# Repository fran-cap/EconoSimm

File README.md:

# EconoSimm
## A low cost Rom for SE/30 machines and compatables
Simply put this allows for a custom rom to be installed inside of a se/30 to skip things like the built in RAM check.
You can also use any extra space to fit in a small system file.

I've based this off of the work of [Doug Brown](https://www.downtowndougbrown.com/category/mac-rom-hacking/).
And GGlabs [MACSIMM](https://gglabs.us/node/2019).

You can find information about making a rom [here](http://www.bigmessowires.com/mac-rom-inator-ii/) (shoutouts to BMOW)
And how to make a custom disk image [here](http://www.bigmessowires.com/2016/07/22/rom-disk-creation-with-rom-inator-ii/).

The max size of any rom image will depend on the size of the flash chips you use but the max is 4 4mb chips or 2MB in total.
You can split any rom file you make into 4 pieces using the tool of your choice and burn that to each of the 4 chips.

## Note: The pcb has to be 1.2MM thick (approx) or it will not fit into a rom socket!

### You can program the chips individually with a standard flash programmer and a 32 PLCC -> dip adapter
BMOW's programmer may work but I have not tested it.

#### I'm not liable if this damages your Macintosh

## Replaces this:

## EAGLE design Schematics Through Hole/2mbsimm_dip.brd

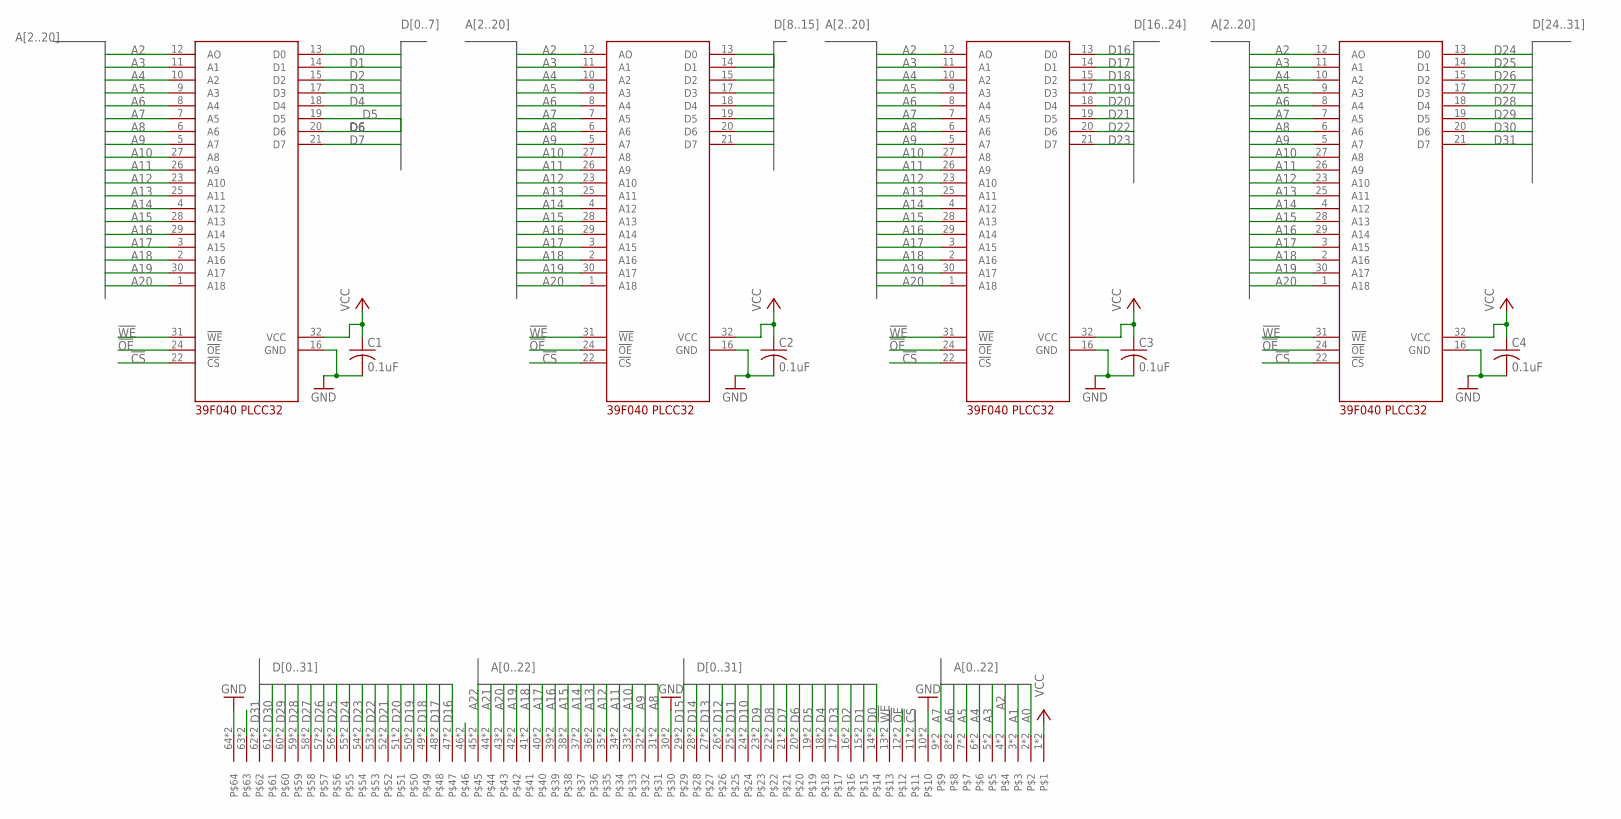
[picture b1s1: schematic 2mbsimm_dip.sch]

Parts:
C1, C2, C3, C4: 0.1uF; C1206
CON1: MYSIMM; SIMM64L
U$1, U$2, U$3, U$4: 39F040-PLCC-SOCKET-DIP; S32

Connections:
!CS: CON1.11, CON1.75, U$1.22 (!CS), U$2.22 (!CS), U$3.22 (!CS), U$4.22 (!CS)
!OE: CON1.12, CON1.76, U$1.24 (!OE), U$2.24 (!OE), U$3.24 (!OE), U$4.24 (!OE)
!WE: CON1.13, CON1.77, U$1.31 (!WE), U$2.31 (!WE), U$3.31 (!WE), U$4.31 (!WE)
A0: CON1.2, CON1.66
A1: CON1.3, CON1.67
A2: CON1.4, CON1.68, U$1.12 (AO), U$2.12 (AO), U$3.12 (AO), U$4.12 (AO)
A3: CON1.5, CON1.69, U$1.11 (A1), U$2.11 (A1), U$3.11 (A1), U$4.11 (A1)
A4: CON1.6, CON1.70, U$1.10 (A2), U$2.10 (A2), U$3.10 (A2), U$4.10 (A2)
A5: CON1.7, CON1.71, U$1.9 (A3), U$2.9 (A3), U$3.9 (A3), U$4.9 (A3)
A6: CON1.8, CON1.72, U$1.8 (A4), U$2.8 (A4), U$3.8 (A4), U$4.8 (A4)
A7: CON1.9, CON1.73, U$1.7 (A5), U$2.7 (A5), U$3.7 (A5), U$4.7 (A5)
A8: CON1.31, CON1.95, U$1.6 (A6), U$2.6 (A6), U$3.6 (A6), U$4.6 (A6)
A9: CON1.32, CON1.96, U$1.5 (A7), U$2.5 (A7), U$3.5 (A7), U$4.5 (A7)
A10: CON1.33, CON1.97, U$1.27 (A8), U$2.27 (A8), U$3.27 (A8), U$4.27 (A8)
A11: CON1.34, CON1.98, U$1.26 (A9), U$2.26 (A9), U$3.26 (A9), U$4.26 (A9)
A12: CON1.35, CON1.99, U$1.23 (A10), U$2.23 (A10), U$3.23 (A10), U$4.23 (A10)
A13: CON1.36, CON1.100, U$1.25 (A11), U$2.25 (A11), U$3.25 (A11), U$4.25 (A11)
A14: CON1.37, CON1.101, U$1.4 (A12), U$2.4 (A12), U$3.4 (A12), U$4.4 (A12)
A15: CON1.38, CON1.102, U$1.28 (A13), U$2.28 (A13), U$3.28 (A13), U$4.28 (A13)
A16: CON1.39, CON1.103, U$1.29 (A14), U$2.29 (A14), U$3.29 (A14), U$4.29 (A14)
A17: CON1.40, CON1.104, U$1.3 (A15), U$2.3 (A15), U$3.3 (A15), U$4.3 (A15)
A18: CON1.41, CON1.105, U$1.2 (A16), U$2.2 (A16), U$3.2 (A16), U$4.2 (A16)
A19: CON1.42, CON1.106, U$1.30 (A17), U$2.30 (A17), U$3.30 (A17), U$4.30 (A17)
A20: CON1.43, CON1.107, U$1.1 (A18), U$2.1 (A18), U$3.1 (A18), U$4.1 (A18)
A21: CON1.44, CON1.108
A22: CON1.45, CON1.109
D0: CON1.14, CON1.78, U$1.13 (D0)
D1: CON1.15, CON1.79, U$1.14 (D1)
D2: CON1.16, CON1.80, U$1.15 (D2)
D3: CON1.17, CON1.81, U$1.17 (D3)
D4: CON1.18, CON1.82, U$1.18 (D4)
D5: CON1.19, CON1.83, U$1.19 (D5)
D6: CON1.20, CON1.84, U$1.20 (D6)
D7: CON1.21, CON1.85, U$1.21 (D7)
D8: CON1.22, CON1.86, U$2.13 (D0)
D9: CON1.23, CON1.87, U$2.14 (D1)
D10: CON1.24, CON1.88, U$2.15 (D2)
D11: CON1.25, CON1.89, U$2.17 (D3)
D12: CON1.26, CON1.90, U$2.18 (D4)
D13: CON1.27, CON1.91, U$2.19 (D5)
D14: CON1.28, CON1.92, U$2.20 (D6)
D15: CON1.29, CON1.93, U$2.21 (D7)
D16: CON1.47, CON1.111, U$3.13 (D0)
D17: CON1.48, CON1.112, U$3.14 (D1)
D18: CON1.49, CON1.113, U$3.15 (D2)
D19: CON1.50, CON1.114, U$3.17 (D3)
D20: CON1.51, CON1.115, U$3.18 (D4)
D21: CON1.52, CON1.116, U$3.19 (D5)
D22: CON1.53, CON1.117, U$3.20 (D6)
D23: CON1.54, CON1.118, U$3.21 (D7)
D24: CON1.55, CON1.119, U$4.13 (D0)
D25: CON1.56, CON1.120, U$4.14 (D1)
D26: CON1.57, CON1.121, U$4.15 (D2)
D27: CON1.58, CON1.122, U$4.17 (D3)
D28: CON1.59, CON1.123, U$4.18 (D4)
D29: CON1.60, CON1.124, U$4.19 (D5)
D30: CON1.61, CON1.125, U$4.20 (D6)
D31: CON1.62, CON1.126, U$4.21 (D7)
GND: C1.2, C2.2, C3.2, C4.2, CON1.10, CON1.30, CON1.64, CON1.74, CON1.94, CON1.128, U$1.16 (GND), U$2.16 (GND), U$3.16 (GND), U$4.16 (GND)
unnamed: CON1.46, CON1.110
UNUSED3: CON1.63, CON1.127
VCC: C1.1, C2.1, C3.1, C4.1, CON1.1, CON1.65, U$1.32 (VCC), U$2.32 (VCC), U$3.32 (VCC), U$4.32 (VCC)

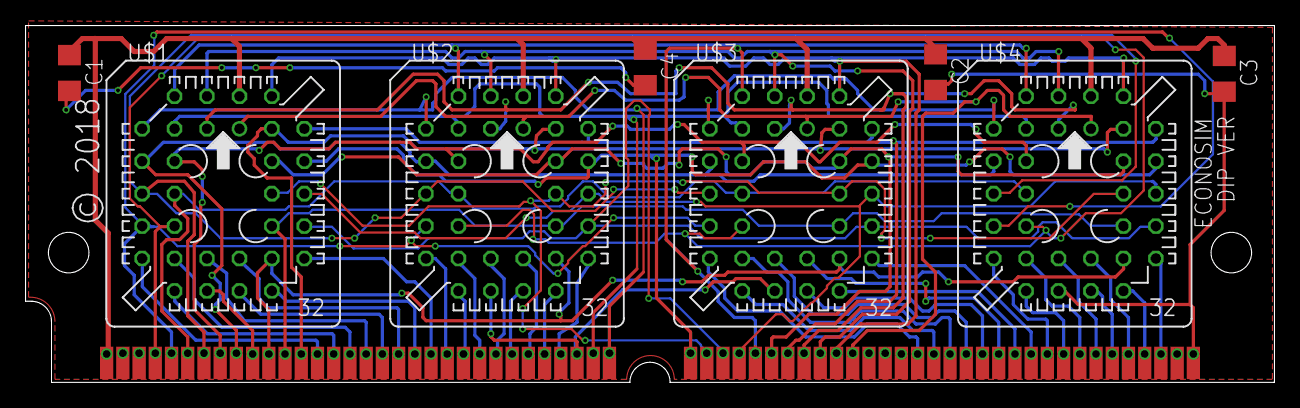
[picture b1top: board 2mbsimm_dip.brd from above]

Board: 2 copper layers, 97.8 x 27.9 mm, 9 parts (0 on the bottom side), 62 nets.

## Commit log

2018-03-10 Formatting :^)
2018-03-11 Added image to readme
2018-03-11 Updated readme again
2018-03-11 Spelling :V
2018-03-28 Added through hole version.
    Decided that some people may not feel comfertable soldering SMD plcc sockets or may not have a hot air station. This solves that problem by being through hole. Still has the SMD caps but they're larg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

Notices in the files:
Schematics Through Hole/2mbsimm_dip.brd:
© 2018
